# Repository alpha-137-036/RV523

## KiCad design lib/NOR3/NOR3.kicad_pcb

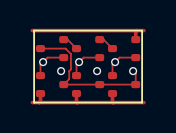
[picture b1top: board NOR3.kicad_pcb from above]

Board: 2 copper layers, 6 parts (0 on the bottom side), 7 nets.

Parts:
N1, N2, N3: NMOS; SOT523
P1, P2, P3: PMOS; SOT523

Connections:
A1: N1.1 (G), P1.1 (G)
A2: N2.1 (G), P2.1 (G)
A3: N3.1 (G), P3.1 (G)
GND: N1.2 (S), N2.2 (S), N3.2 (S)
Y: N1.3 (D), N2.3 (D), N3.3 (D), P1.3 (D)
int1: P1.2 (S), P2.3 (D)
int2: P2.2 (S), P3.3 (D)

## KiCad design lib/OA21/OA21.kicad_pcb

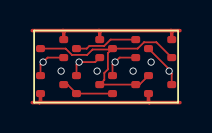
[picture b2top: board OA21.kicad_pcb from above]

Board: 2 copper layers, 8 parts (0 on the bottom side), 9 nets.

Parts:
not1.N1: NMOS; SOT523
not1.P1: PMOS; SOT523
oai.N1, oai.N2, oai.N3: NMOS; SOT523
oai.P1, oai.P2, oai.P3: PMOS; SOT523

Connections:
A: oai.N1.1 (G), oai.P1.1 (G)
B1: oai.N2.1 (G), oai.P2.1 (G)
B2: oai.N3.1 (G), oai.P3.1 (G)
GND: not1.N1.2 (S), oai.N1.2 (S)
VDD: not1.P1.2 (S), oai.P1.2 (S), oai.P2.2 (S)
Y: not1.N1.3 (D), not1.P1.3 (D)
Y_N: not1.N1.1 (G), not1.P1.1 (G), oai.N2.3 (D), oai.N3.3 (D), oai.P1.3 (D), oai.P3.3 (D)
oai.intB: oai.P2.3 (D), oai.P3.2 (S)
oai.intN: oai.N1.3 (D), oai.N2.2 (S), oai.N3.2 (S)
